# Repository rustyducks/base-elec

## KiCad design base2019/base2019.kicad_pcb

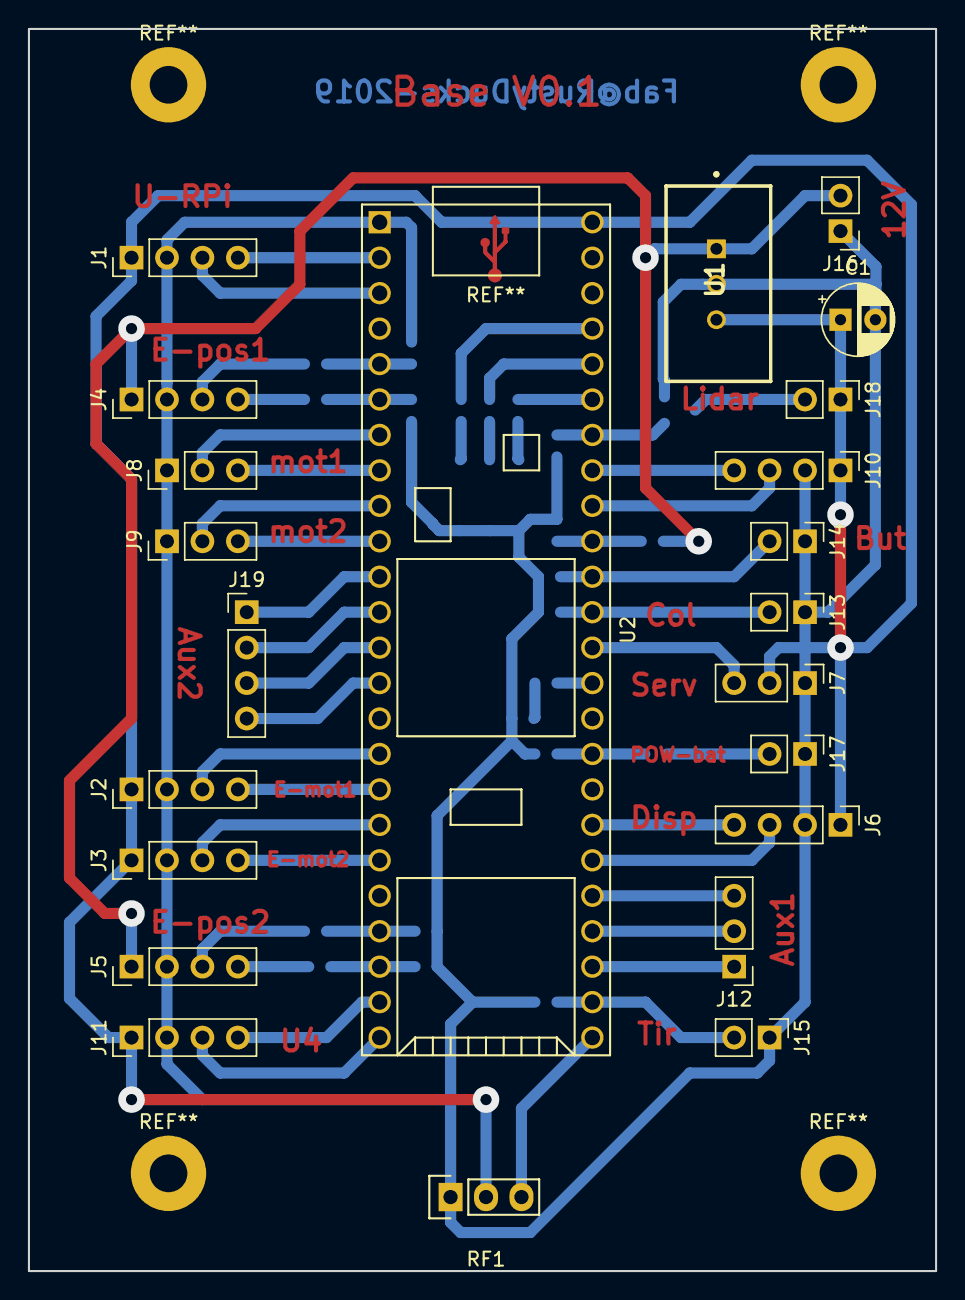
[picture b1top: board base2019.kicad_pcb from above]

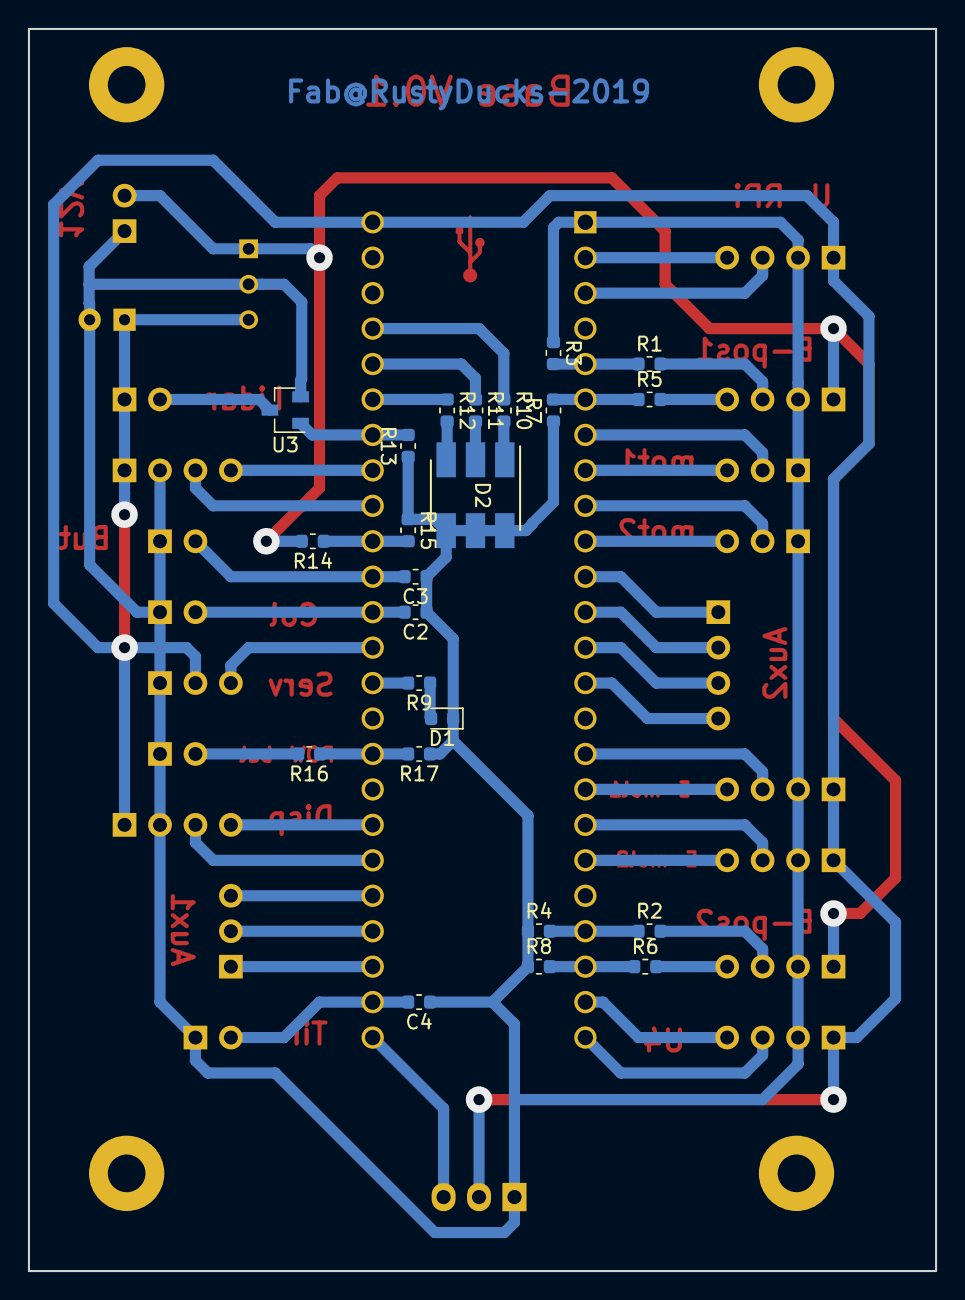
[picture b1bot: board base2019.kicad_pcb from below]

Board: 2 copper layers, 65.0 x 89.0 mm, 46 parts (23 on the bottom side), 52 nets.

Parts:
C1: 10u; CP_Radial_D5.0mm_P2.50mm
C2, C3, C4: 100n; C_0603_1608Metric
D1: LED; LED_0603_1608Metric
D2: CLP6C-FKB; PLCC6_CLP6C-FKB
J1: UART_RPi; PinHeader_1x04_P2.54mm_Vertical
J2: EncMot1; PinHeader_1x04_P2.54mm_Vertical
J3: EncMot2; PinHeader_1x04_P2.54mm_Vertical
J4: EncPos1; PinHeader_1x04_P2.54mm_Vertical
J5: EncPos2; PinHeader_1x04_P2.54mm_Vertical
J6: Display; PinHeader_1x04_P2.54mm_Vertical
J7: servo; PinHeader_1x03_P2.54mm_Vertical
J8: Mot1; PinHeader_1x03_P2.54mm_Vertical
J9: Mot2; PinHeader_1x03_P2.54mm_Vertical
J10: I2C; PinHeader_1x04_P2.54mm_Vertical
J11: UARTx; PinHeader_1x04_P2.54mm_Vertical
J12: AUX; PinHeader_1x03_P2.54mm_Vertical
J13: color_btn; PinHeader_1x02_P2.54mm_Vertical
J14: user_btn; PinHeader_1x02_P2.54mm_Vertical
J15: tirette; PinHeader_1x02_P2.54mm_Vertical
J16: sig_bat; PinHeader_1x02_P2.54mm_Vertical
J17: power_bat; PinHeader_1x02_P2.54mm_Vertical
J18: Lidar; PinHeader_1x02_P2.54mm_Vertical
J19: AUX2; PinHeader_1x04_P2.54mm_Vertical
R1, R2, R5, R6: 8k; R_0603_1608Metric
R3, R4, R7, R8, R15, R17: 2.2k; R_0603_1608Metric
R9: R; R_0603_1608Metric
R10: 65; R_0603_1608Metric
R11, R12: 5; R_0603_1608Metric
R13, R14, R16: 10k; R_0603_1608Metric
RF1: RF_Transmitter_433_MHz
U1: TSR_2-2450; TSR-2
U2: Teensy3.5; Teensy35_36
U3: IRLML6344; SOT-23

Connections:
+5V: C1.1, J1.1, J2.1, J3.1, J6.1, J7.2, J10.1, J11.1, J18.1, RF1.2, U1.3, U2.53
+12P: J17.2, R16.2
+12V: J4.1, J5.1, J16.2, R14.2, U1.1
/433_data: RF1.3, U2.30
/Enc1A: R1.1, R3.2, U2.5
/Enc1B: R5.1, R7.2, U2.6
/Enc2A: R2.1, R4.2, U2.21
/Enc2B: R6.1, R8.2, U2.22
/EncMot1A: J2.3, U2.16
/EncMot1B: J2.4, U2.17
/EncMot2A: J3.3, U2.18
/EncMot2B: J3.4, U2.19
/Mot1Dir: J8.3, U2.8
/Mot1Pwm: J8.2, U2.7
/Mot2Dir: J9.3, U2.10
/Mot2Pwm: J9.2, U2.9
/PowMeas: R16.1, R17.2, U2.38
/RX4: J11.4, U2.23
/RX_Rpi: J1.4, U2.2
/SCL0: J10.4, U2.46
/SDA0: J10.3, U2.45
/Servo: J7.3, U2.41
/SigMeas: R14.1, R15.2, U2.44
/TX4: J11.3, U2.24
/TX_Rpi: J1.3, U2.3
/aux1: J12.1, U2.32
/aux2: J12.2, U2.33
/aux3: J12.3, U2.34
/aux4: J19.1, U2.11
/aux5: J19.2, U2.12
/aux6: J19.3, U2.13
/aux7: J19.4, U2.14
/color: C2.2, J13.2, U2.42
/display_CLK: J6.4, U2.36
/display_DIO: J6.3, U2.35
/lidarSpeed: R13.2, U2.47, U3.1
/tirette: C4.2, J15.2, U2.31
/user_btn: C3.2, J14.2, U2.43
GND: C1.2, C2.1, C3.1, C4.1, D1.1, D2.4, D2.5, D2.6, J1.2, J2.2, J3.2, J4.2, J5.2, J6.2, J7.1, J8.1, J9.1, J10.2, J11.2, J13.1, J14.1, J15.1, J16.1, J17.1, R3.1, R4.1, R7.1, R8.1, R13.1, R15.1, R17.1, RF1.1, U1.2, U2.1, U3.2
unnamed: D1.2, R9.1
unnamed: D2.1, R10.2
unnamed: D2.2, R11.2
unnamed: D2.3, R12.2
unnamed: J4.3, R1.2
unnamed: J4.4, R5.2
unnamed: J5.3, R2.2
unnamed: J5.4, R6.2
unnamed: J18.2, U3.3
unnamed: R9.2, U2.40
unnamed: R10.1, U2.50
unnamed: R11.1, U2.49
unnamed: R12.1, U2.48

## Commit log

2019-03-26 First commit; Adds libraries.
2019-03-26 Schematics V0.1
2019-03-26 Adds pcb.
2019-03-28 Fix trace error.
2022-02-04 latest changes
